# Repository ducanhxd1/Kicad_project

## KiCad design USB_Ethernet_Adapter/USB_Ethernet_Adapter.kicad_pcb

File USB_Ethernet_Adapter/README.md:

# Bộ chuyển đổi USB sang Ethernet

Dự án thiết kế một bo mạch chuyển đổi **USB 3.0 sang Ethernet Gigabit**, được vẽ bằng KiCad. Bo mạch dùng chip **Microchip LAN7800/Y9X** để nối USB với mạng Ethernet, có cổng USB Type-B ở một đầu và cổng RJ45 ở đầu còn lại.

## Hình ảnh bo mạch

| Mặt trước | Mặt sau |
| --- | --- |
|  |  |

## Thiết kế gồm những gì?

- **USB:** cổng USB 3.0 Type-B.
- **Ethernet:** LAN7800/Y9X hỗ trợ giao tiếp 10/100/1000 Mbps, kết nối với jack RJ45 tích hợp biến áp HR911130A.
- **Mạch phụ trợ:** thạch anh 25 MHz và LED báo trạng thái mạng.
- **PCB:** thiết kế 4 lớp; tài liệu có thông tin stackup và thiết lập trở kháng cho các đường tín hiệu vi sai.

## Trở kháng cặp vi sai

Các đường tín hiệu tốc độ cao được thiết kế theo trở kháng vi sai đặc trưng của giao tiếp:

- **90 Ω cho USB 3.0 SuperSpeed:** áp dụng cho các cặp phát/thu `SSTX` và `SSRX`.
- **100 Ω cho Ethernet:** áp dụng cho các cặp tín hiệu mạng nối giữa LAN7800 và biến áp trong jack HR911130A.

Ảnh dưới đây ghi lại khoảng cách giữa các đường mạch vi sai trên layout PCB:

### Cặp 90 Ω

### Cặp 100 Ω

Với stackup JLCPCB **JLC0416IH-3313** trong ảnh, calculator cho kết quả cặp 90 Ω không coplanar trên lớp L1, tham chiếu lớp L2: trace rộng **0,1572 mm**, gap **0,22 mm**.

Các kích thước này phụ thuộc vào stackup thực tế, độ dày đồng và lớp tham chiếu. Khi đổi stackup hoặc nhà sản xuất, hãy nhập lại cấu hình vào calculator và xác nhận khả năng kiểm soát trở kháng với nhà sản xuất; không dùng lại width/gap như thông số cố định.

### Thiết lập trong KiCad

**Physical Stackup:** project khai báo PCB 4 lớp đồng với vật liệu FR4 và độ dày tổng khoảng 1,584 mm.

**Net Classes:** project có các class `DP_90R` và `DP_100R`. Ảnh thiết lập thể hiện width lần lượt là 0,16 mm và 0,13 mm, cùng gap 0,22 mm. Đây là thông số luật thiết kế trong KiCad; cần đối chiếu với calculator theo stackup thực tế trước khi sản xuất.

## Cấu trúc dự án

| Thư mục | Nội dung |
| --- | --- |
| `01Docs/IMG/` | Hình ảnh bo mạch và tài liệu tham khảo về stackup, net class, trở kháng |
| `01Docs/LIB/3D/` | Model 3D của linh kiện |
| `01Docs/LIB/Footprints/` | Footprint KiCad |
| `01Docs/LIB/Symbols/` | Symbol KiCad |
| `02Schematic/` | Bản PDF schematic và các lớp PCB đã xuất để xem nhanh |
| `03PCBLayout/` | Project KiCad, schematic và PCB có thể chỉnh sửa |
| `04Manufacturing/ibom/` | BOM tương tác, hỗ trợ tra linh kiện và vị trí lắp trên PCB |
| `04Manufacturing/gerber_to_order/` | Các gói Gerber đóng gói theo định dạng đặt PCB của nhiều nhà sản xuất |
| `05FimwareTest/` | Khu vực dành cho firmware và kiểm thử; hiện chưa có file |

## Bắt đầu xem dự án

- **Xem sơ đồ mạch:** mở [`schematic.pdf`](02Schematic/schematic.pdf).
- **Xem các lớp PCB:** mở `top_layer.pdf`, `layer2.pdf`, `layer3.pdf` hoặc `bottom_layer.pdf` trong `02Schematic/`.
- **Chỉnh sửa thiết kế:** cài KiCad và mở project [`USB_Ethernet_Adapter.kicad_pro`](03PCBLayout/USB_Ethernet_Adapter.kicad_pro).
- **Tra cứu linh kiện:** mở [BOM tương tác](04Manufacturing/ibom/ibom.html) bằng trình duyệt.
- **Đặt chế tạo PCB:** chọn gói ZIP tương ứng với nhà sản xuất trong `04Manufacturing/gerber_to_order/`.

## Trạng thái

Repository hiện có thiết kế KiCad, tài liệu PDF, BOM tương tác và các gói Gerber để gửi nhà sản xuất. Các gói Gerber là dữ liệu xuất từ thiết kế, không đồng nghĩa bo mạch đã được chế tạo hoặc kiểm thử. Thư mục firmware/kiểm thử hiện chưa có nội dung; cần kiểm tra ERC/DRC và đối chiếu yêu cầu của nhà sản xuất trước khi đặt hàng.

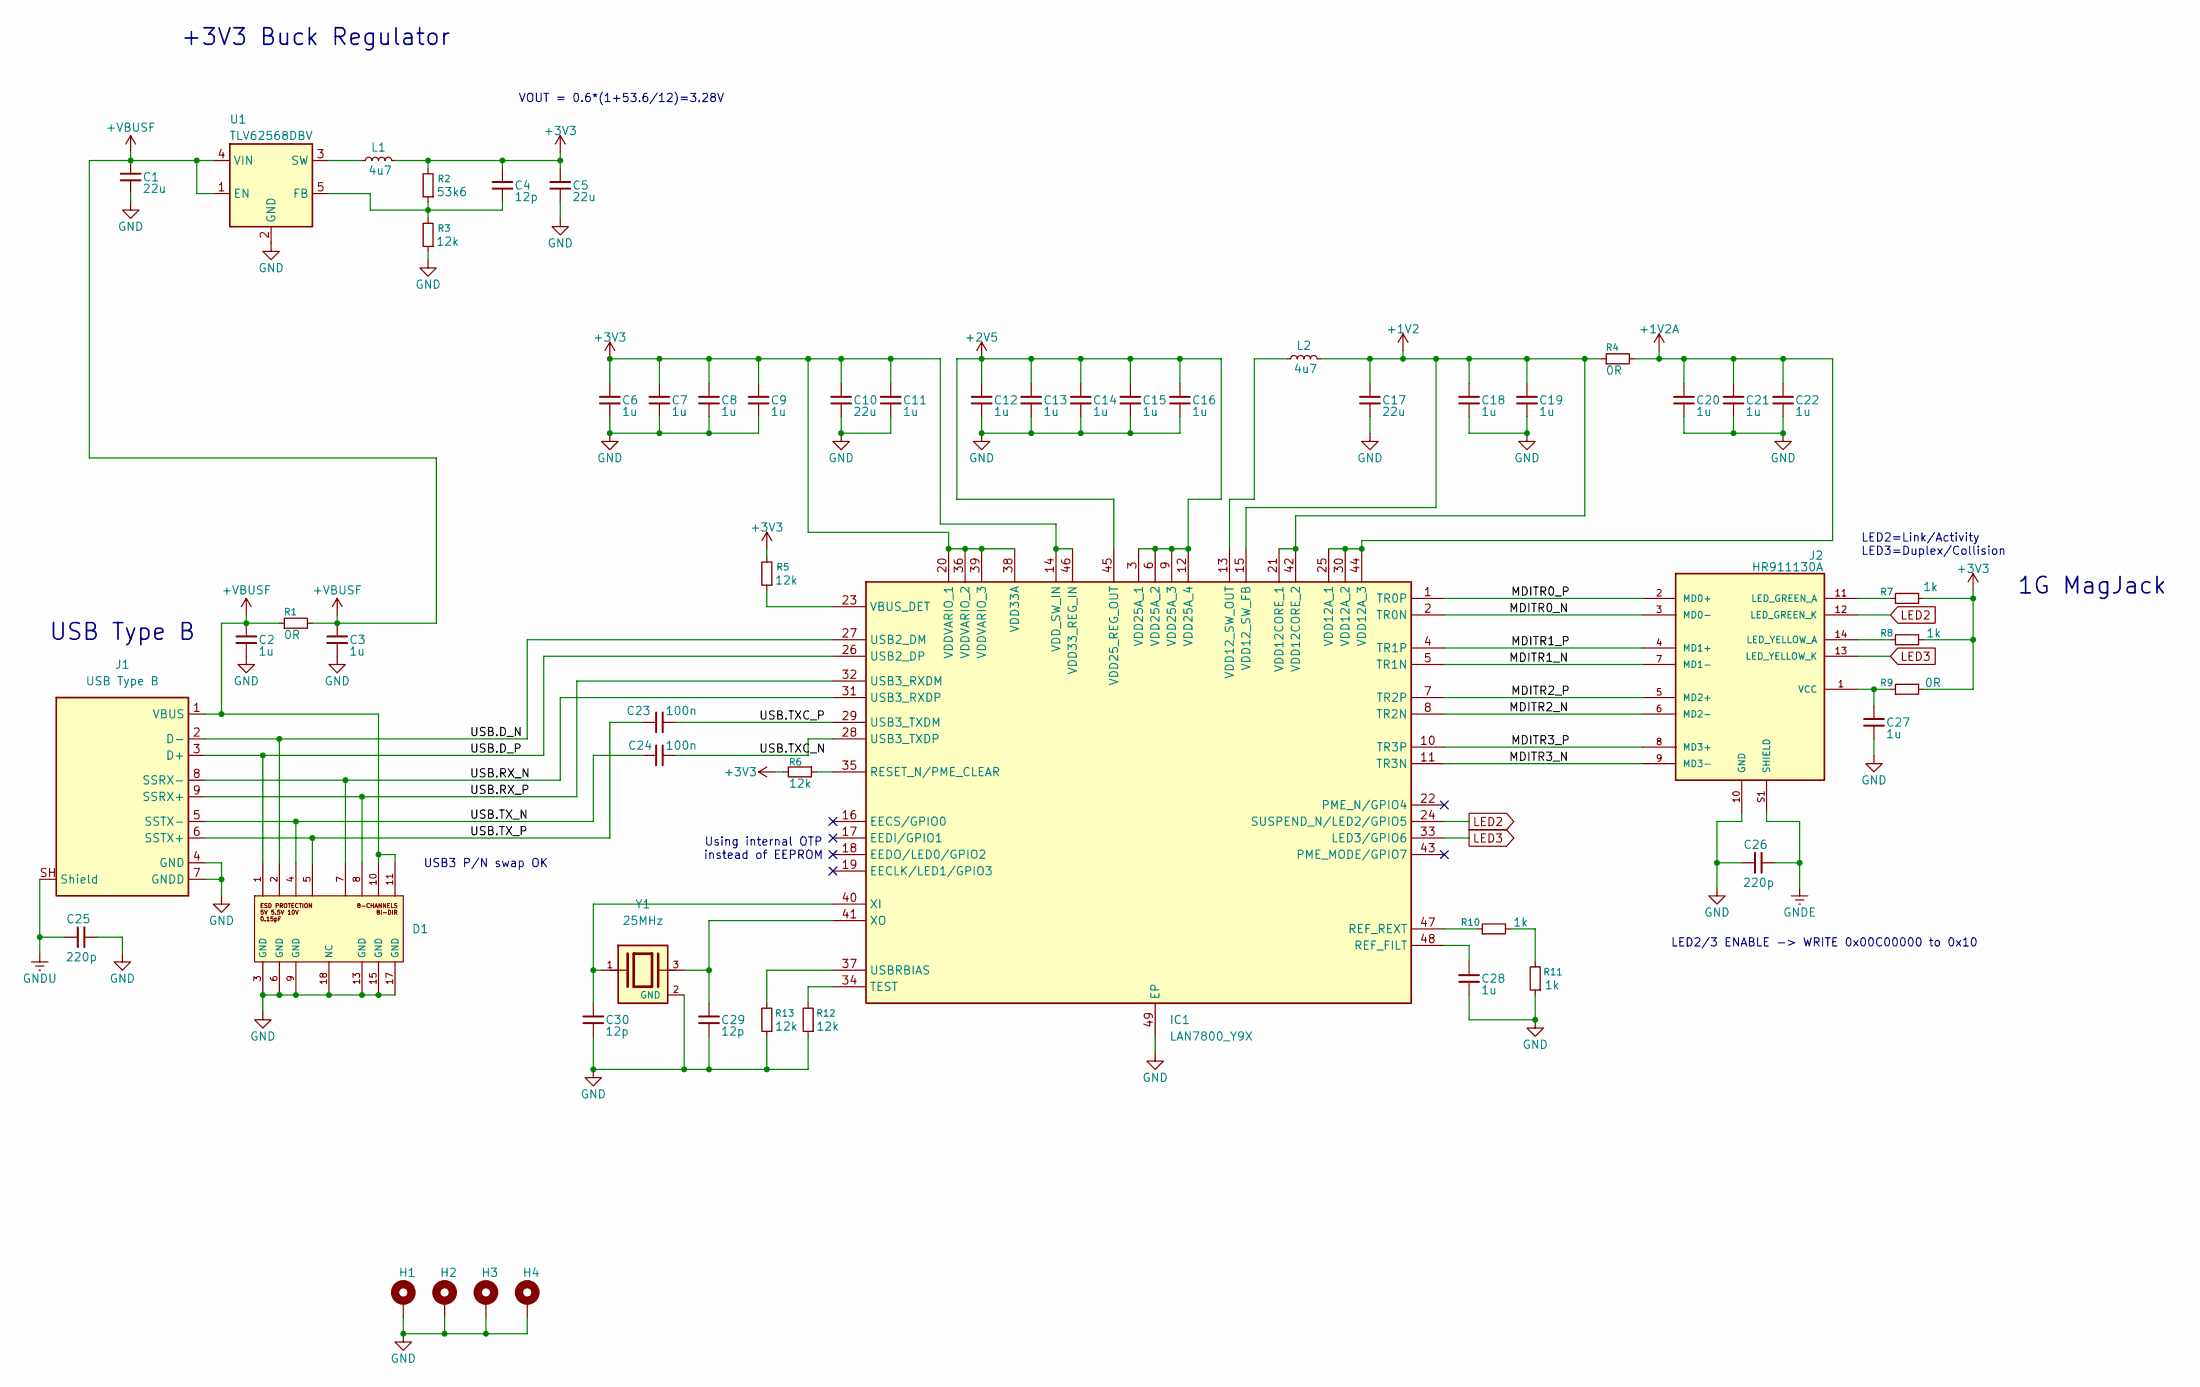
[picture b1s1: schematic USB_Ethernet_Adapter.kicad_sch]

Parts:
C1, C5, C10, C17: 22u; C_0402_1005Metric
C2, C3, C6, C7, C8, C9, C11, C12, C13, C14, C15, C16, C18, C19, C20, C21, C22, C27, C28: 1u; C_0402_1005Metric
C4, C29, C30: 12p; C_0402_1005Metric
C23, C24: 100n; C_0402_1005Metric
C25, C26: 220p; C_1206_3216Metric
D1: ESD7008MUTAG
H1, H2, H3, H4: MountingHole_Pad; MountingHole_3.5mm_Pad_Via
IC1: LAN7800_Y9X; 48-SQFN; Manufacturer_Part_Number LAN7800/Y9X
J1: USB Type B; KUSBX-BS1N9-1-BL30
J2: HR911130A; HANRUN_HR911130A; PARTREV A
L1, L2: 4u7; L_0402_1005Metric
R1, R4, R9: 0R; R_0402_1005Metric
R2: 53k6; R_0402_1005Metric
R3, R5, R6, R12, R13: 12k; R_0402_1005Metric
R7, R8, R10, R11: 1k; R_0402_1005Metric
U1: TLV62568DBV; SOT-23-5
Y1: 25MHz; XTAL_C3E-25.000-18-3030-X-R; PARTREV N/A

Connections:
+1V2: C17.1, C18.1, C19.1, IC1.15 (VDD12_SW_FB), IC1.21 (VDD12CORE_1), IC1.42 (VDD12CORE_2), L2.2, R4.1
+1V2A: C20.1, C21.1, C22.1, IC1.25 (VDD12A_1), IC1.30 (VDD12A_2), IC1.44 (VDD12A_3), R4.2
+2V5: C12.1, C13.1, C14.1, C15.1, C16.1, IC1.3 (VDD25A_1), IC1.6 (VDD25A_2), IC1.9 (VDD25A_3), IC1.12 (VDD25A_4), IC1.45 (VDD25_REG_OUT)
+3V3: C4.1, C5.1, C6.1, C7.1, C8.1, C9.1, C10.1, C11.1, IC1.14 (VDD_SW_IN), IC1.20 (VDDVARIO_1), IC1.36 (VDDVARIO_2), IC1.38 (VDD33A), IC1.39 (VDDVARIO_3), IC1.46 (VDD33_REG_IN), L1.2, R2.2, R5.2, R6.2, R7.2, R8.2, R9.2
+VBUSF: C1.1, C2.1, C3.1, D1.10, D1.11, J1.1 (VBUS), R1.1, R1.2, U1.1 (EN), U1.4 (VIN)
/MDITR0_N: IC1.2 (TR0N), J2.3 (MD0-)
/MDITR0_P: IC1.1 (TR0P), J2.2 (MD0+)
/MDITR1_N: IC1.5 (TR1N), J2.7 (MD1-)
/MDITR1_P: IC1.4 (TR1P), J2.4 (MD1+)
/MDITR2_N: IC1.8 (TR2N), J2.6 (MD2-)
/MDITR2_P: IC1.7 (TR2P), J2.5 (MD2+)
/MDITR3_N: IC1.11 (TR3N), J2.9 (MD3-)
/MDITR3_P: IC1.10 (TR3P), J2.8 (MD3+)
/USB.D_N: D1.2, IC1.27 (USB2_DM), J1.2 (D-)
/USB.D_P: D1.1, IC1.26 (USB2_DP), J1.3 (D+)
/USB.RX_N: D1.7, IC1.31 (USB3_RXDP), J1.8 (SSRX-)
/USB.RX_P: D1.8, IC1.32 (USB3_RXDM), J1.9 (SSRX+)
/USB.TXC_N: C24.2, IC1.28 (USB3_TXDP)
/USB.TXC_P: C23.2, IC1.29 (USB3_TXDM)
/USB.TX_N: C24.1, D1.4, J1.5 (SSTX-)
/USB.TX_P: C23.1, D1.5, J1.6 (SSTX+)
GND: C1.2, C2.2, C3.2, C5.2, C6.2, C7.2, C8.2, C9.2, C10.2, C11.2, C12.2, C13.2, C14.2, C15.2, C16.2, C17.2, C18.2, C19.2, C20.2, C21.2, C22.2, C25.2, C26.1, C27.2, C28.2, C29.2, C30.2, D1.3 (GND), D1.6 (GND), D1.9 (GND), D1.13 (GND), D1.15 (GND), D1.17 (GND), D1.18 (NC), H1.1 (1_1), H2.1 (1_1), H3.1 (1_1), H4.1 (1_1), IC1.49 (EP), J1.4 (GND), J1.7 (GNDD), J2.10 (GND), R3.1, R11.1, R12.1, R13.1, U1.2 (GND), Y1.2 (GND), Y1.4 (GND)
GNDE: C26.2, J2.S1 (SHIELD), J2.S2 (SHIELD)
GNDU: C25.1, J1.SH (Shield)
LED2: IC1.24 (SUSPEND_N/LED2/GPIO5), J2.12 (LED_GREEN_K)
LED3: IC1.33 (LED3/GPIO6), J2.13 (LED_YELLOW_K)
unnamed: C28.1, IC1.48 (REF_FILT)
unnamed: IC1.47 (REF_REXT), R10.1
unnamed: IC1.35 (RESET_N/PME_CLEAR), R6.1
unnamed: IC1.34 (TEST), R12.2
unnamed: IC1.37 (USBRBIAS), R13.2
unnamed: IC1.23 (VBUS_DET), R5.1
unnamed: IC1.13 (VDD12_SW_OUT), L2.1
unnamed: C30.1, IC1.40 (XI), Y1.1
unnamed: C29.1, IC1.41 (XO), Y1.3
unnamed: J2.11 (LED_GREEN_A), R7.1
unnamed: J2.14 (LED_YELLOW_A), R8.1
unnamed: C27.1, J2.1 (VCC), R9.1
unnamed: R10.2, R11.2
unnamed: C4.2, R2.1, R3.2, U1.5 (FB)
unnamed: L1.1, U1.3 (SW)

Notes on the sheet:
VOUT = 0.6*(1+53.6/12)=3.28V
LED2/3 ENABLE -> WRITE 0x00C00000 to 0x10
USB3 P/N swap OK
LED2=Link/Activity LED3=Duplex/Collision
Using internal OTP instead of EEPROM
+3V3 Buck Regulator
USB Type B
1G MagJack

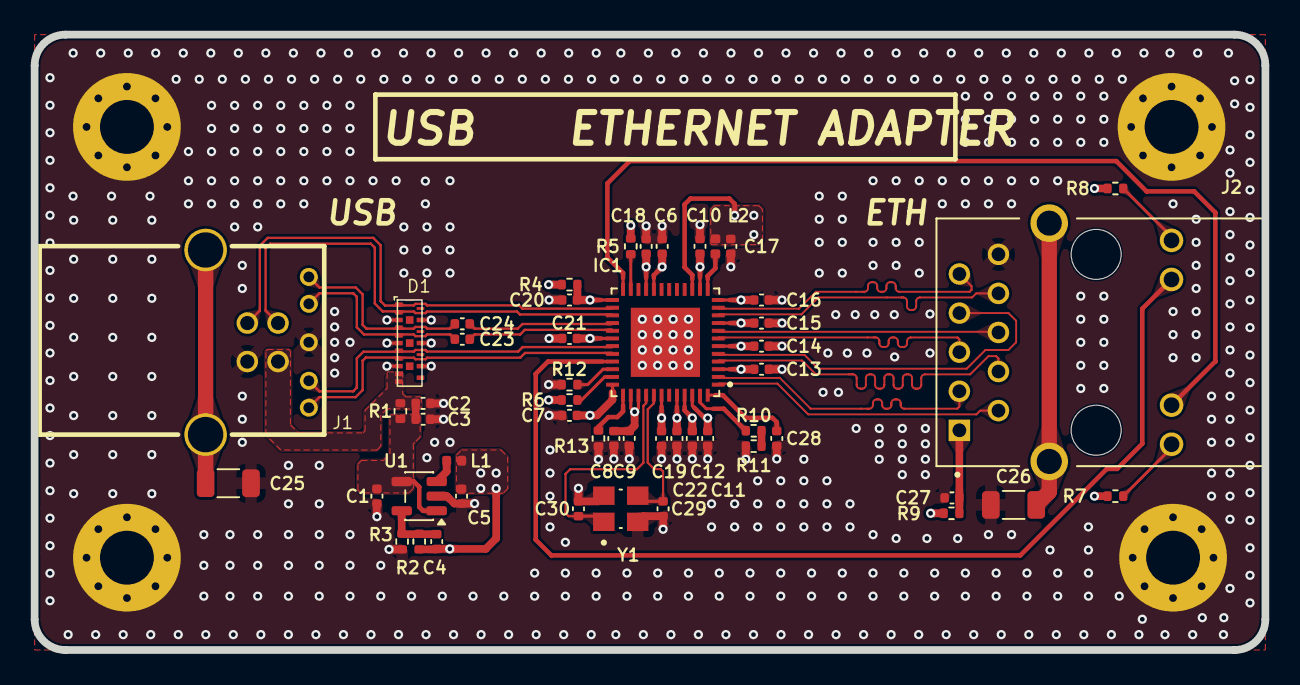
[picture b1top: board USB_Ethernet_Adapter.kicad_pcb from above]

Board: 4 copper layers, 80.0 x 40.0 mm, 55 parts (0 on the bottom side), 41 nets.

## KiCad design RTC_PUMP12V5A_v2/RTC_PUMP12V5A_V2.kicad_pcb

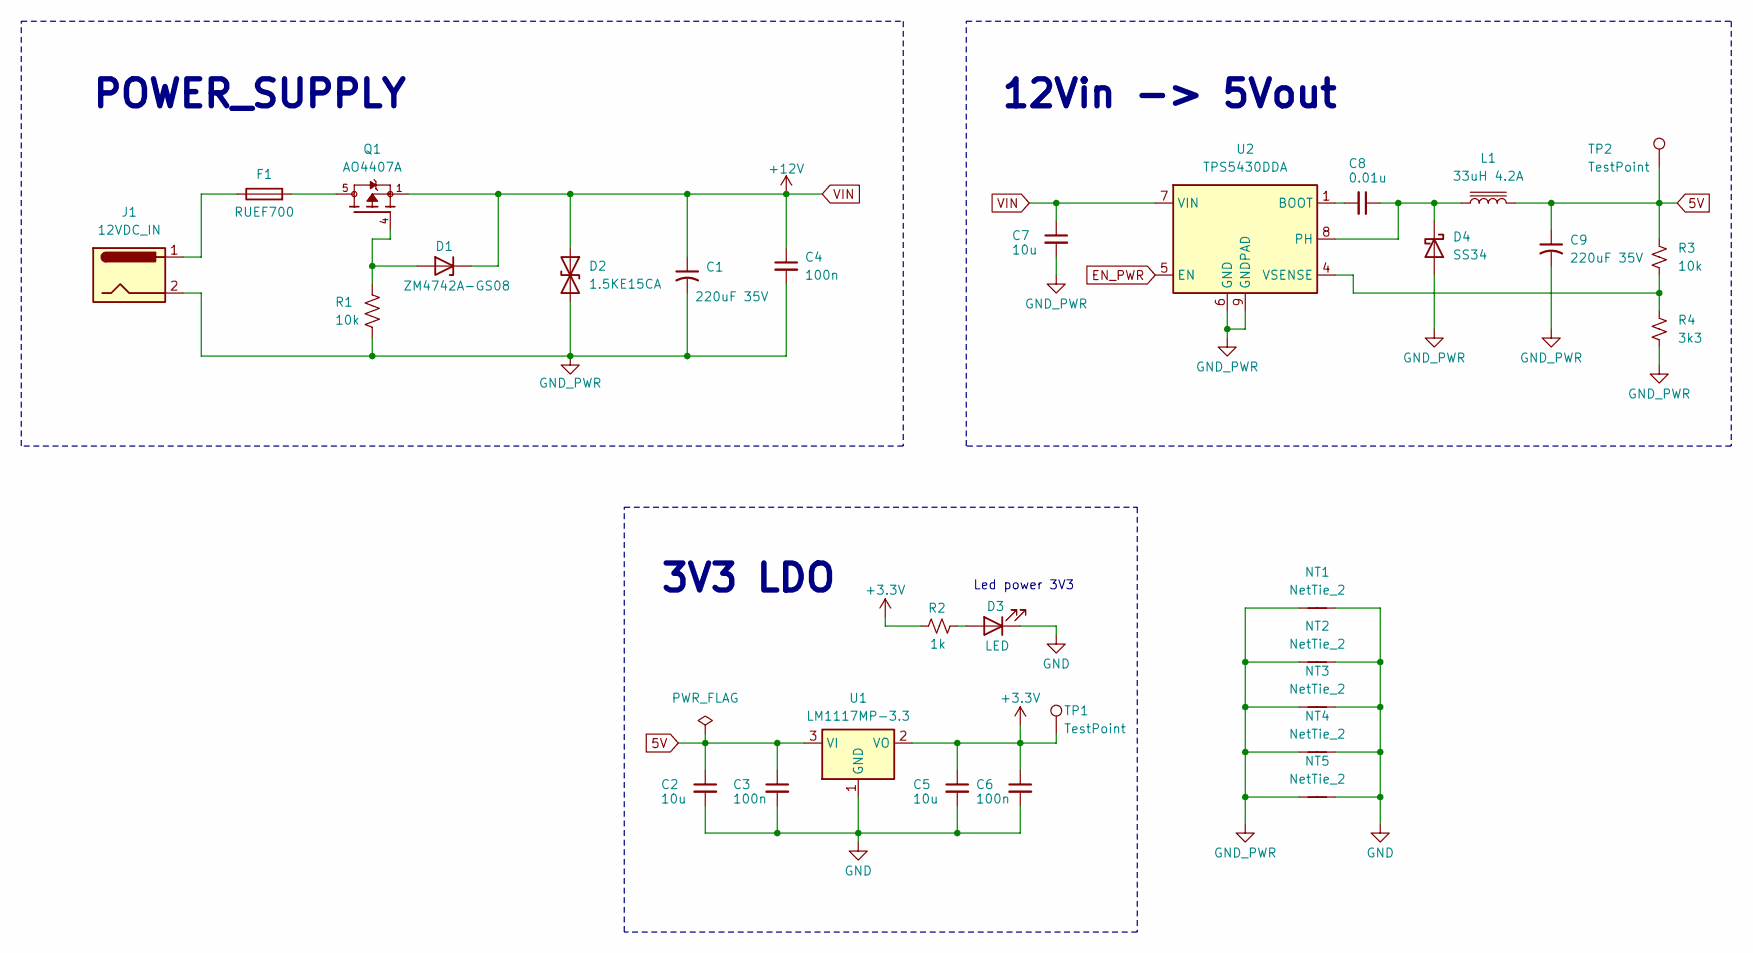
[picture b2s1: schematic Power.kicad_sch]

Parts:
C1, C9: 220uF 35V; CP_Elec_8x10.5
C2, C5, C7: 10u; C_0805_2012Metric
C3, C4, C6: 100n; C_0805_2012Metric
C8: 0.01u; C_0805_2012Metric
D1: ZM4742A-GS08; D_MELF_Handsoldering
D2: 1.5KE15CA; D_DO-201AD_P15.24mm_Horizontal
D3: LED; LED_0805_2012Metric
D4: SS34; D_SMA
F1: RUEF700; FUSRR505W81L660T250H1360
J1: 12VDC_IN; BarrelJack_Horizontal
L1: 33uH 4.2A; L_Bourns_SRR1208_12.7x12.7mm
NT1, NT2, NT3, NT4, NT5: NetTie_2; NetTie-2_SMD_Pad2.0mm
Q1: AO4407A; SOIC127P600X175-8N; PARTREV I
R1, R3: 10k; R_0805_2012Metric
R2: 1k; R_0805_2012Metric
R4: 3k3; R_0805_2012Metric
TP1, TP2: TestPoint; Pin_D1.0mm_L10.0mm
U1: LM1117MP-3.3; SOT-223-3_TabPin2
U2: TPS5430DDA; TI_SO-PowerPAD-8_ThermalVias

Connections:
5V: C2.1, C3.1, C9.1, L1.2, R3.1, TP2.1, U1.3 (VI); also elsewhere on the board
+3.3V: C5.1, C6.1, R2.1, TP1.1, U1.2 (VO); also elsewhere on the board
EN_PWR: U2.5 (EN)
GND: C2.2, C3.2, C5.2, C6.2, D3.1 (K), NT1.2, NT2.2, NT3.2, NT4.2, NT5.2, U1.1 (GND); also elsewhere on the board
GND_PWR: C1.2, C4.2, C7.2, C9.2, D2.2 (A2), D4.2 (A), J1.2, J1.3, NT1.1, NT2.1, NT3.1, NT4.1, NT5.1, R1.2, R4.2, U2.6 (GND), U2.9 (GNDPAD); also elsewhere on the board
unnamed: D1.2 (A), Q1.4, R1.1
unnamed: D3.2 (A), R2.2
unnamed: C8.1, D4.1 (K), L1.1, U2.8 (PH)
unnamed: F1.1, J1.1
unnamed: F1.2, Q1.5, Q1.6, Q1.7, Q1.8
unnamed: C8.2, U2.1 (BOOT)
unnamed: R3.2, R4.1, U2.4 (VSENSE)
VIN: C1.1, C4.1, C7.1, D1.1 (K), D2.1 (A1), Q1.1, Q1.2, Q1.3, U2.7 (VIN); also elsewhere on the board

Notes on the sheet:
3V3 LDO
Led power 3V3
POWER_SUPPLY
12Vin -> 5Vout

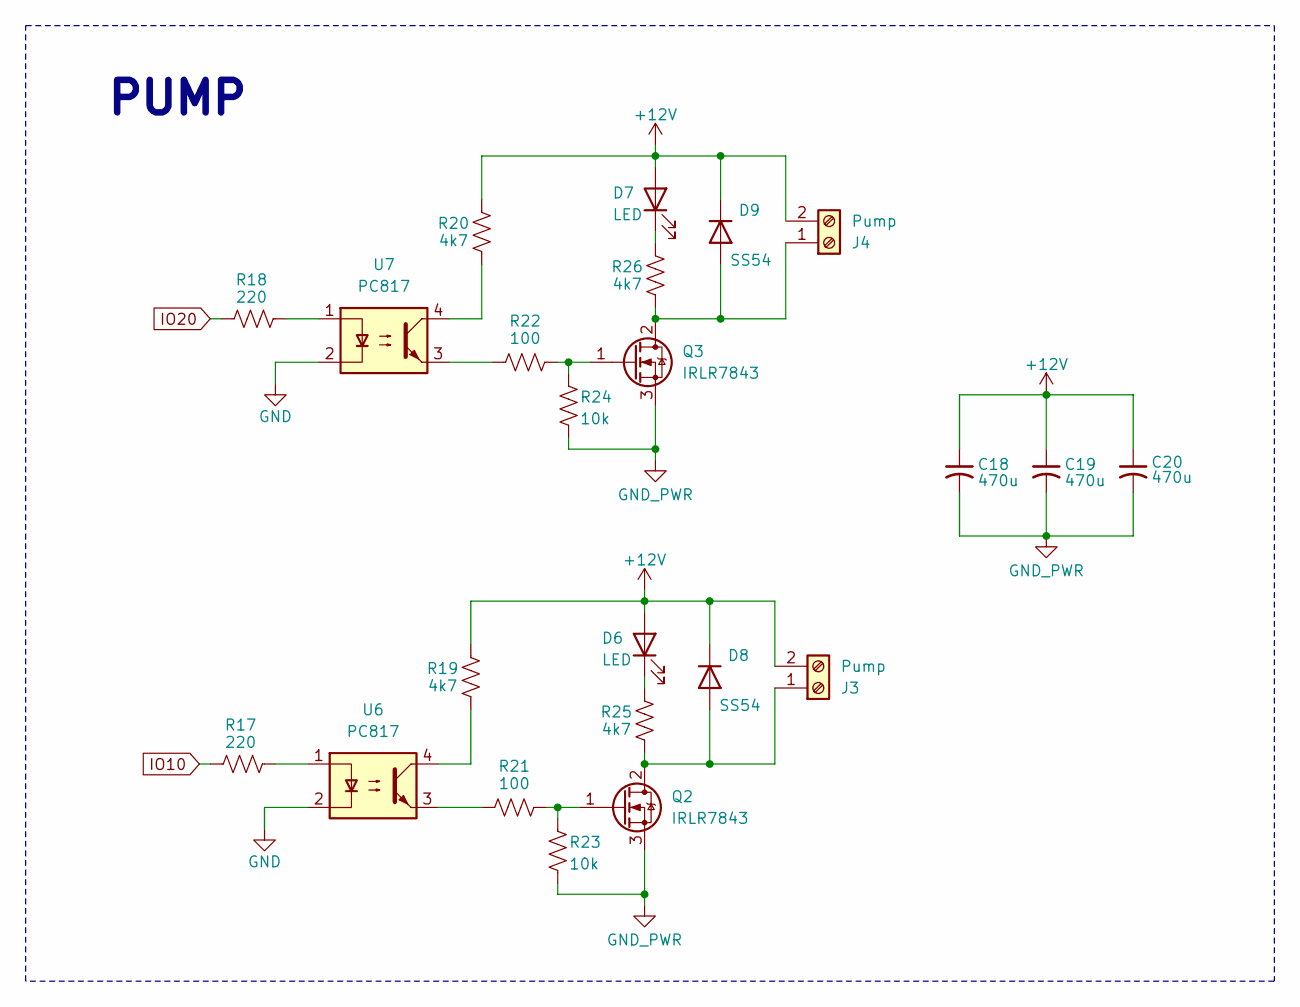
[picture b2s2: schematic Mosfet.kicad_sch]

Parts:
C18, C19, C20: 470u; CP_Radial_D10.0mm_P5.00mm
D6, D7: LED; LED_0805_2012Metric
D8, D9: SS54; Diode SS54
J3, J4: Pump; PhoenixContact_MC_1,5_2-G-3.81_1x02_P3.81mm_Horizontal
Q2, Q3: IRLR7843; TO-252-2
R17, R18: 220; R_0805_2012Metric
R19, R20, R25, R26: 4k7; R_0805_2012Metric
R21, R22: 100; R_0805_2012Metric
R23, R24: 10k; R_0805_2012Metric
U6, U7: PC817; DIP-4_W7.62mm_SMDSocket_SmallPads

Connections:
GND: U6.2, U7.2; also elsewhere on the board
GND_PWR: C18.2, C19.2, C20.2, Q2.3 (S), Q3.3 (S), R23.1, R24.1; also elsewhere on the board
IO10: R17.1; also elsewhere on the board
IO20: R18.1; also elsewhere on the board
unnamed: D6.1 (K), R25.2
unnamed: D7.1 (K), R26.2
unnamed: D8.2 (A), J3.1, Q2.2 (D), R25.1
unnamed: D9.2 (A), J4.1, Q3.2 (D), R26.1
unnamed: Q2.1 (G), R21.2, R23.2
unnamed: Q3.1 (G), R22.2, R24.2
unnamed: R17.2, U6.1
unnamed: R18.2, U7.1
unnamed: R19.1, U6.4
unnamed: R20.1, U7.4
unnamed: R21.1, U6.3
unnamed: R22.1, U7.3
VIN: C18.1, C19.1, C20.1, D6.2 (A), D7.2 (A), D8.1 (K), D9.1 (K), J3.2, J4.2, R19.2, R20.2; also elsewhere on the board

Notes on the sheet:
PUMP

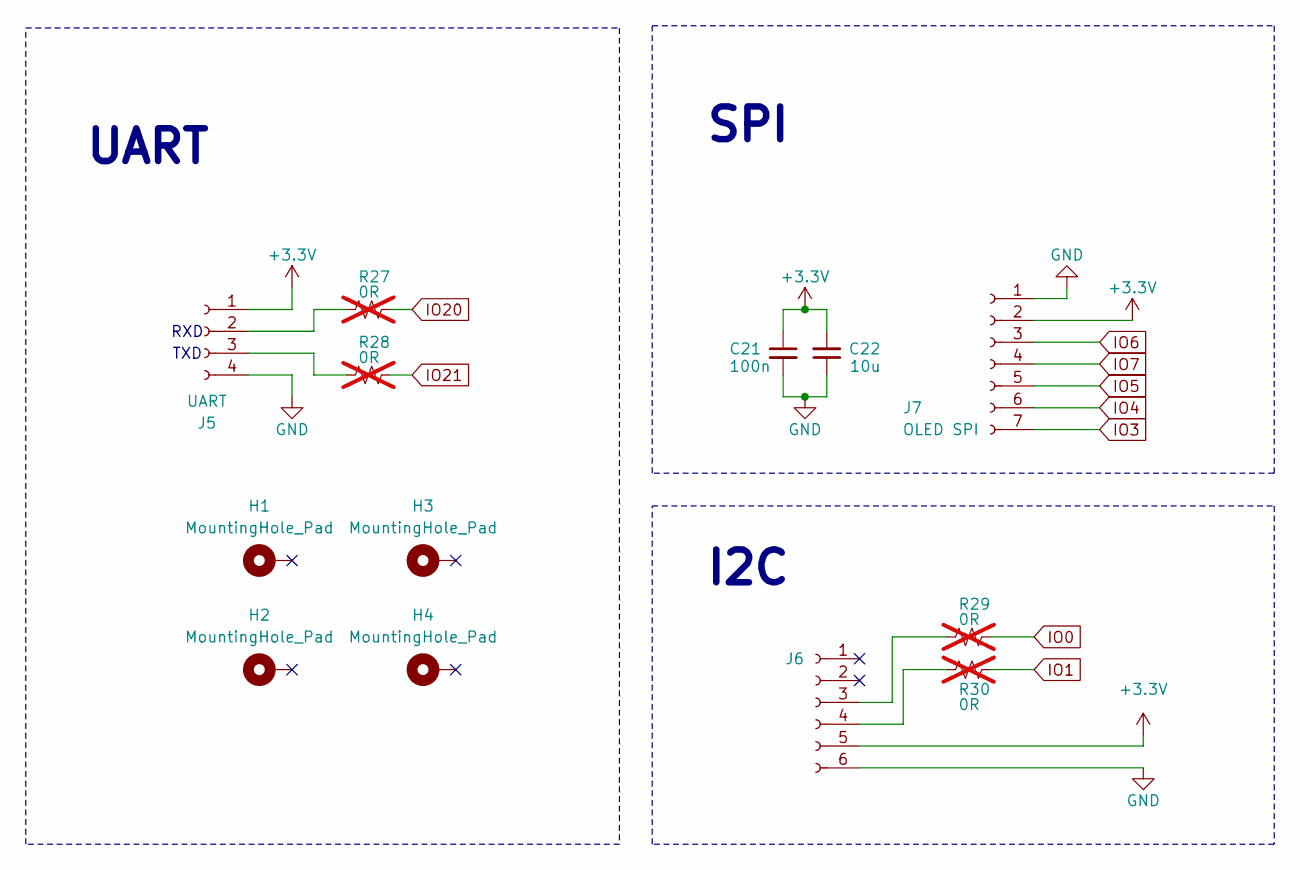
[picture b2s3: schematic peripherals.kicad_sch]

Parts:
C21: 100n; C_0805_2012Metric
C22: 10u; C_0805_2012Metric
H1, H2, H3, H4: MountingHole_Pad; MountingHole_3.5mm_Pad
J5: UART; JST_XH_B4B-XH-A_1x04_P2.50mm_Vertical
J6: Conn_01x06_Socket; PinSocket_1x06_P2.54mm_Vertical
J7: OLED SPI; Adafruit_SSD1306
R27, R28, R29, R30: 0R; R_0805_2012Metric; not fitted

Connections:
+3.3V: C21.1, C22.2, J5.1, J6.5, J7.2; also elsewhere on the board
GND: C21.2, C22.1, J5.4, J6.6, J7.1; also elsewhere on the board
IO0: R29.1; also elsewhere on the board
IO1: R30.1; also elsewhere on the board
IO3: J7.7; also elsewhere on the board
IO4: J7.6; also elsewhere on the board
IO5: J7.5; also elsewhere on the board
IO6: J7.3; also elsewhere on the board
IO7: J7.4; also elsewhere on the board
IO20: R27.1; also elsewhere on the board
IO21: R28.1; also elsewhere on the board
unnamed: J5.2, R27.2
unnamed: J5.3, R28.2
unnamed: J6.3, R29.2
unnamed: J6.4, R30.2

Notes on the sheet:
UART
TXD
I2C
RXD
SPI

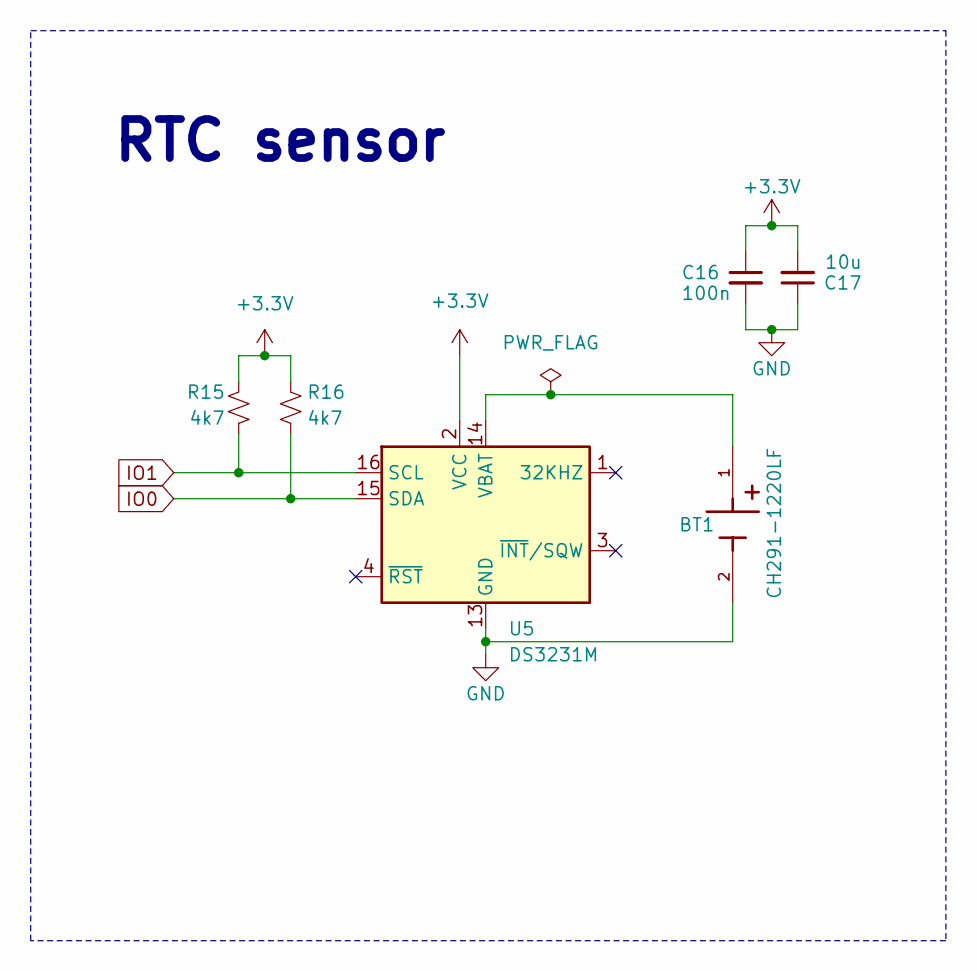
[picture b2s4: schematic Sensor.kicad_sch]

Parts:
BT1: CH291-1220LF; CR1220; PARTREV A
C16: 100n; C_0805_2012Metric
C17: 10u; C_0805_2012Metric
R15, R16: 4k7; R_0805_2012Metric
U5: DS3231M; SOIC-16W_7.5x10.3mm_P1.27mm

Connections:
+3.3V: C16.1, C17.2, R15.2, R16.2, U5.2 (VCC); also elsewhere on the board
GND: BT1.2, C16.2, C17.1, U5.5 (GND), U5.6 (GND), U5.7 (GND), U5.8 (GND), U5.9 (GND), U5.10 (GND), U5.11 (GND), U5.12 (GND), U5.13 (GND); also elsewhere on the board
IO0: R16.1, U5.15 (SDA); also elsewhere on the board
IO1: R15.1, U5.16 (SCL); also elsewhere on the board
unnamed: BT1.1, U5.14 (VBAT)

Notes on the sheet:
RTC sensor

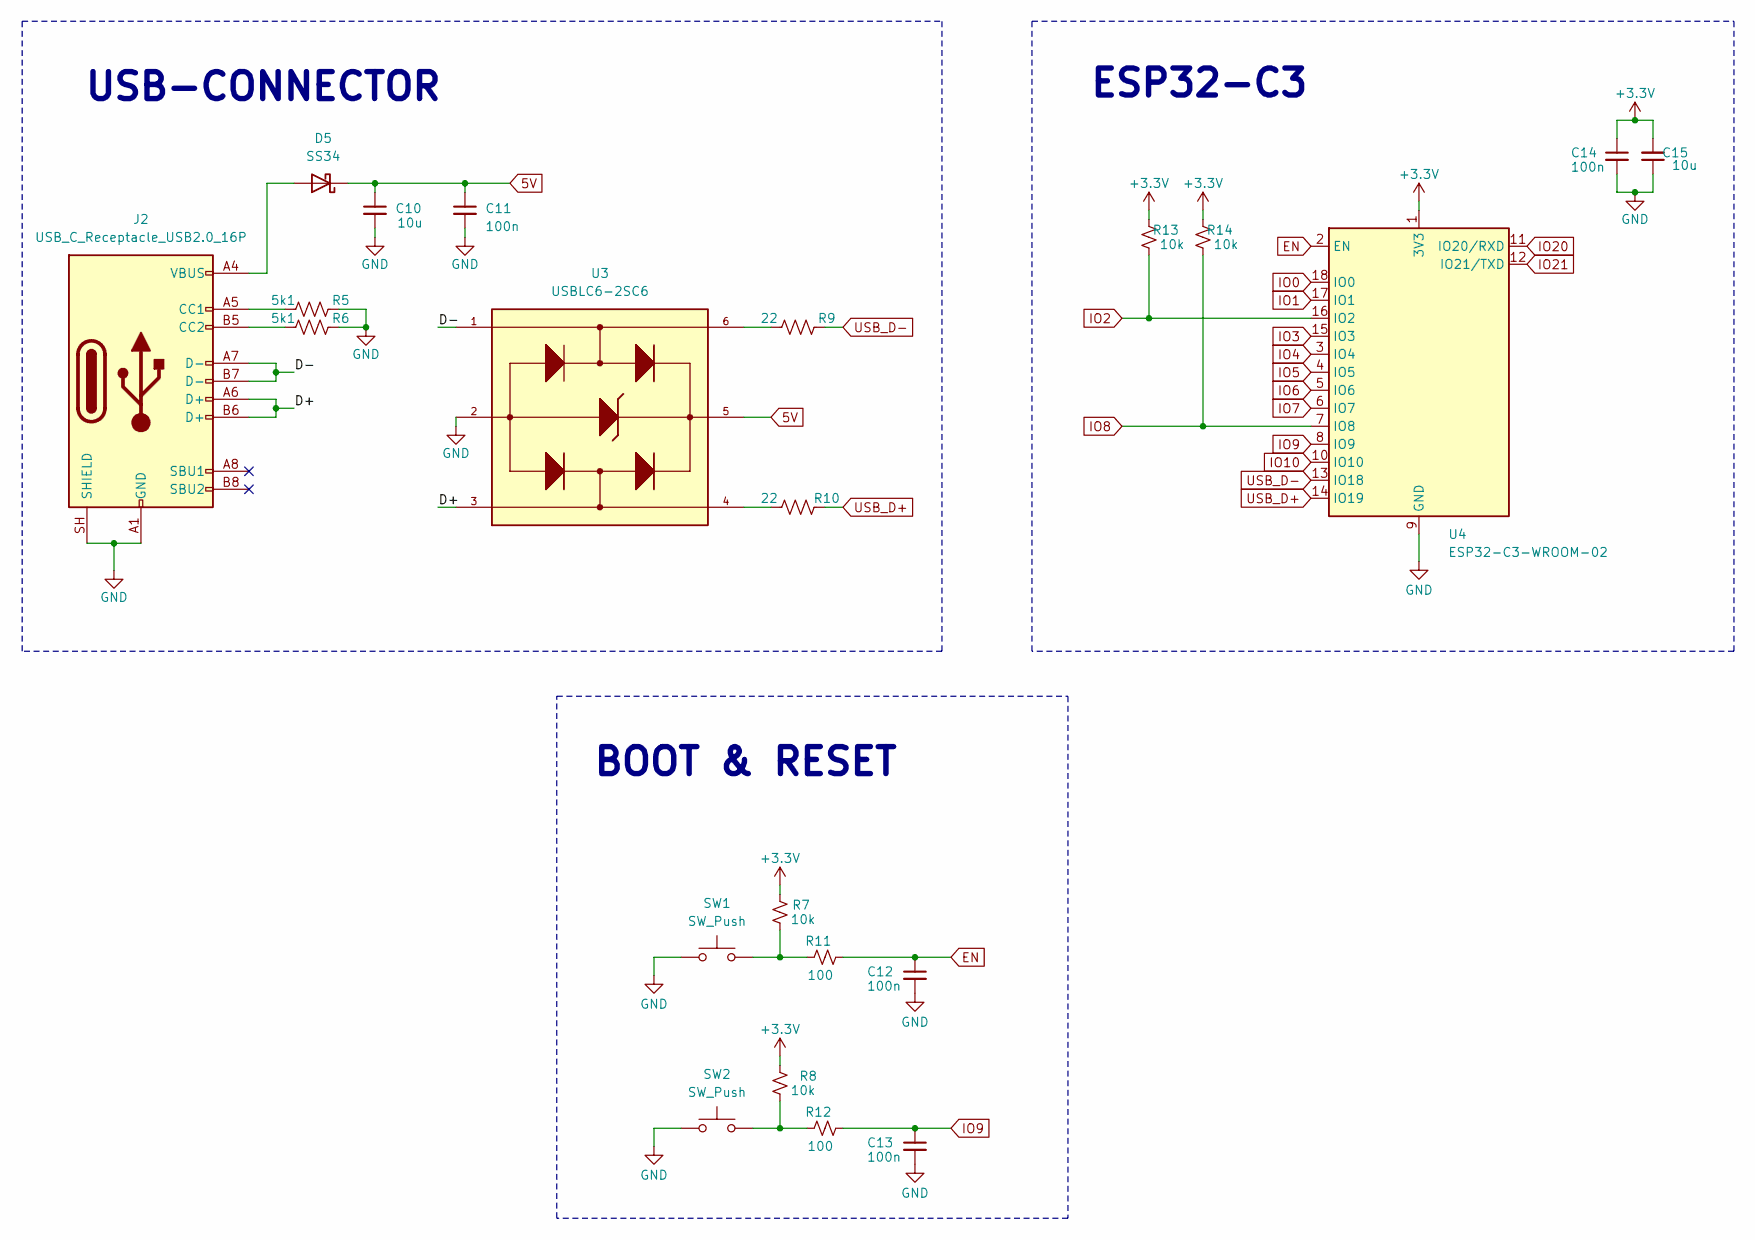
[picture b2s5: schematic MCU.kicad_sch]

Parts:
C10, C15: 10u; C_0805_2012Metric
C11, C12, C13, C14: 100n; C_0805_2012Metric
D5: SS34; D_SMA
J2: USB_C_Receptacle_USB2.0_16P; USB_C_Receptacle_HRO_TYPE-C-31-M-12
R5, R6: 5k1; R_0805_2012Metric
R7, R8, R13, R14: 10k; R_0805_2012Metric
R9, R10: 22; R_0805_2012Metric
R11, R12: 100; R_0805_2012Metric
SW1, SW2: SW_Push; SW_Tactile_SPST_NO_Straight_CK_PTS636Sx25SMTRLFS
U3: USBLC6-2SC6; SOT95P280X145-6N
U4: ESP32-C3-WROOM-02

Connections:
5V: C10.1, C11.1, D5.1 (K), U3.5; also elsewhere on the board
+3.3V: C14.1, C15.2, R7.2, R8.2, R13.2, R14.2, U4.1 (3V3); also elsewhere on the board
/MCU/D+: J2.A6 (D+), J2.B6 (D+), U3.3
/MCU/D-: J2.A7 (D-), J2.B7 (D-), U3.1
EN: C12.1, R11.2, U4.2 (EN)
GND: C10.2, C11.2, C12.2, C13.2, C14.2, C15.1, J2.A1 (GND), J2.A12 (GND), J2.B1 (GND), J2.B12 (GND), J2.SH (SHIELD), R5.2, R6.2, SW1.1, SW2.1, U3.2, U4.9 (GND), U4.19 (GND); also elsewhere on the board
IO0: U4.18 (IO0); also elsewhere on the board
IO1: U4.17 (IO1); also elsewhere on the board
IO2: R13.1, U4.16 (IO2)
IO3: U4.15 (IO3); also elsewhere on the board
IO4: U4.3 (IO4); also elsewhere on the board
IO5: U4.4 (IO5); also elsewhere on the board
IO6: U4.5 (IO6); also elsewhere on the board
IO7: U4.6 (IO7); also elsewhere on the board
IO8: R14.1, U4.7 (IO8)
IO9: C13.1, R12.2, U4.8 (IO9)
IO10: U4.10 (IO10); also elsewhere on the board
IO20: U4.11 (IO20/RXD); also elsewhere on the board
IO21: U4.12 (IO21/TXD); also elsewhere on the board
unnamed: D5.2 (A), J2.A4 (VBUS), J2.A9 (VBUS), J2.B4 (VBUS), J2.B9 (VBUS)
unnamed: J2.A5 (CC1), R5.1
unnamed: J2.B5 (CC2), R6.1
unnamed: R9.1, U3.6
unnamed: R10.1, U3.4
unnamed: R7.1, R11.1, SW1.2
unnamed: R8.1, R12.1, SW2.2
USB_D+: R10.2, U4.14 (IO19)
USB_D-: R9.2, U4.13 (IO18)

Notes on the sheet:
BOOT & RESET
ESP32-C3
USB-CONNECTOR

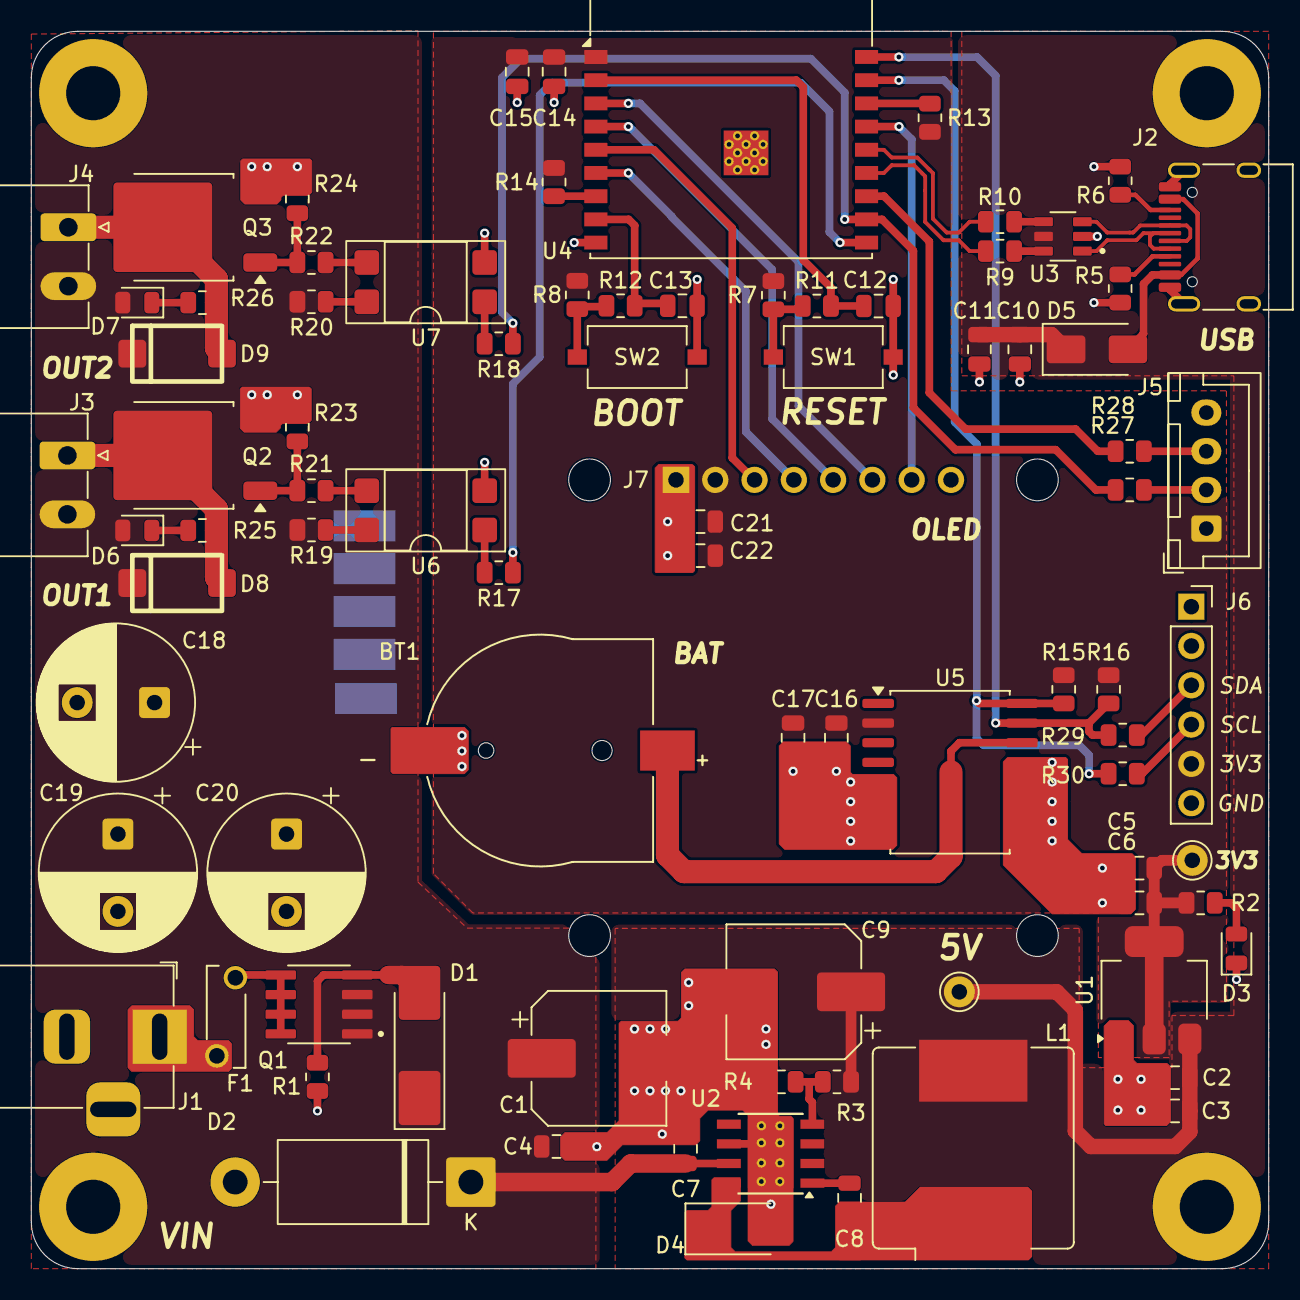
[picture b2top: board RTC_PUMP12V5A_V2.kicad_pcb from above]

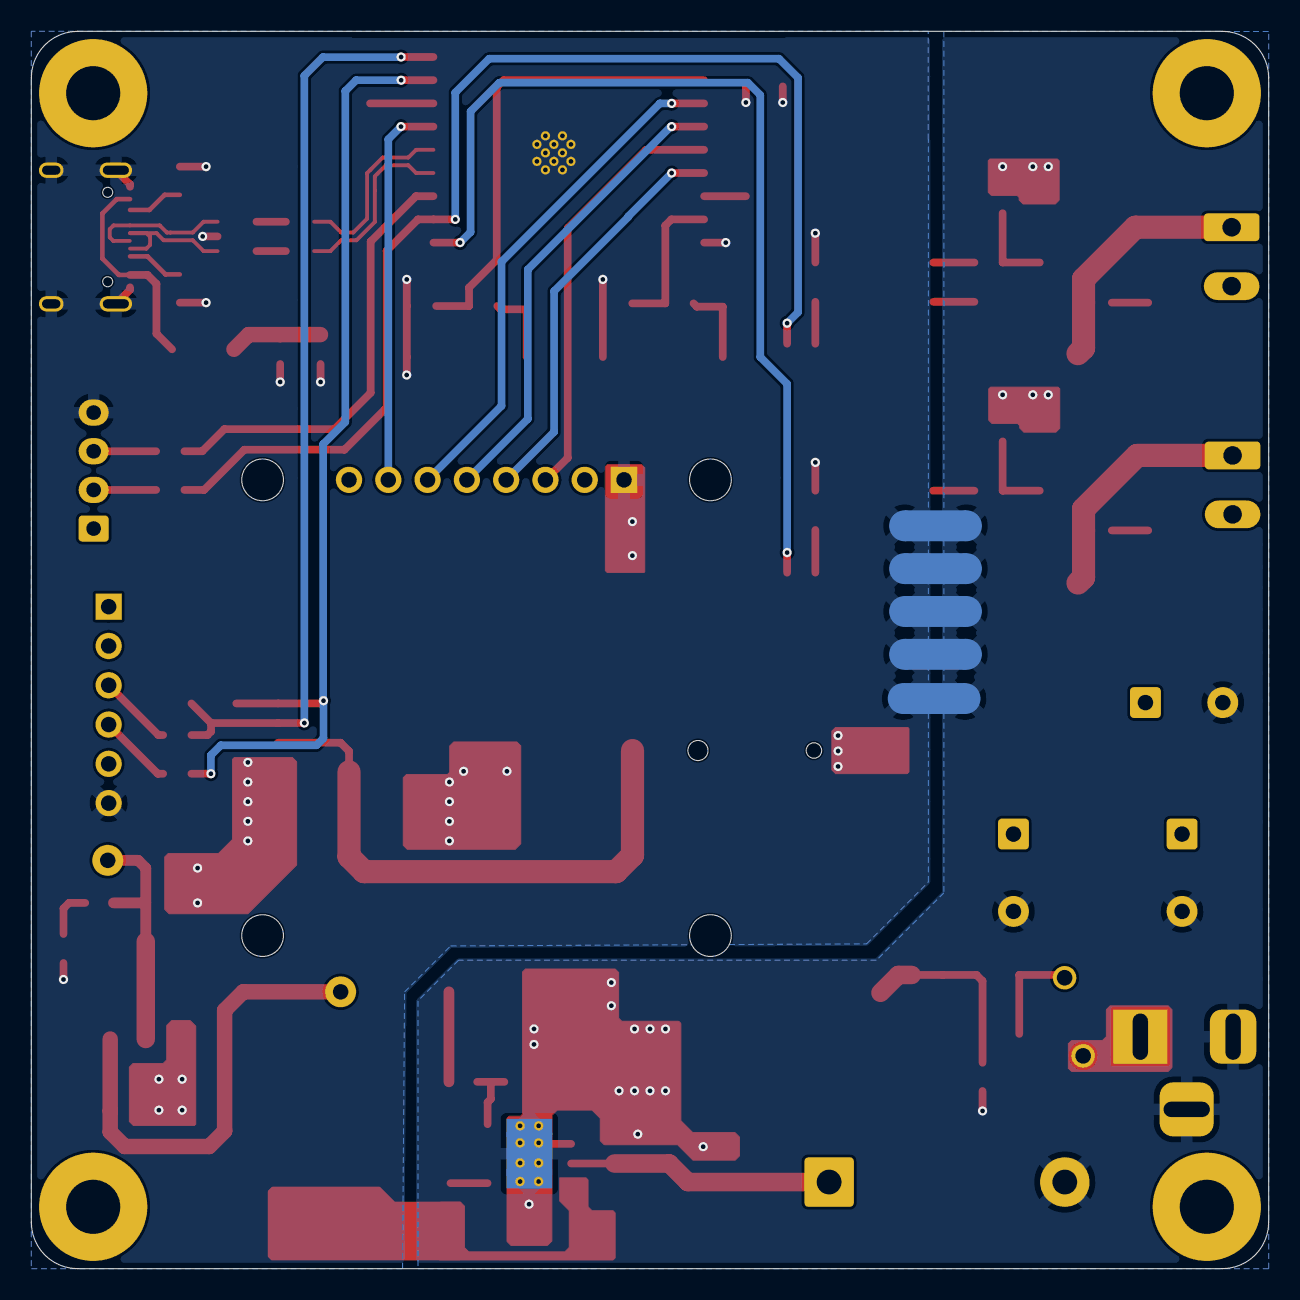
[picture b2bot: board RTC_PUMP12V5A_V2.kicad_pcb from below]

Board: 2 copper layers, 80.0 x 80.0 mm, 94 parts (5 on the bottom side), 54 nets.

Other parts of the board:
3V3, 5V: TestPoint; Pin_D1.0mm_L10.0mm

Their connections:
5V: 5V.1 (1_1); also elsewhere on the board
+3.3V: 3V3.1 (1_1); also elsewhere on the board
